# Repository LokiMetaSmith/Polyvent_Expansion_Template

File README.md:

# Polyvent_Expansion_Template
This project is a bare template board for generating new Polyvent Expansion Cards

<a href="Schematic.gif">Schematic screen shot     
</a>  

<a href="Schematic.gif">PCB screen shot   
</a>

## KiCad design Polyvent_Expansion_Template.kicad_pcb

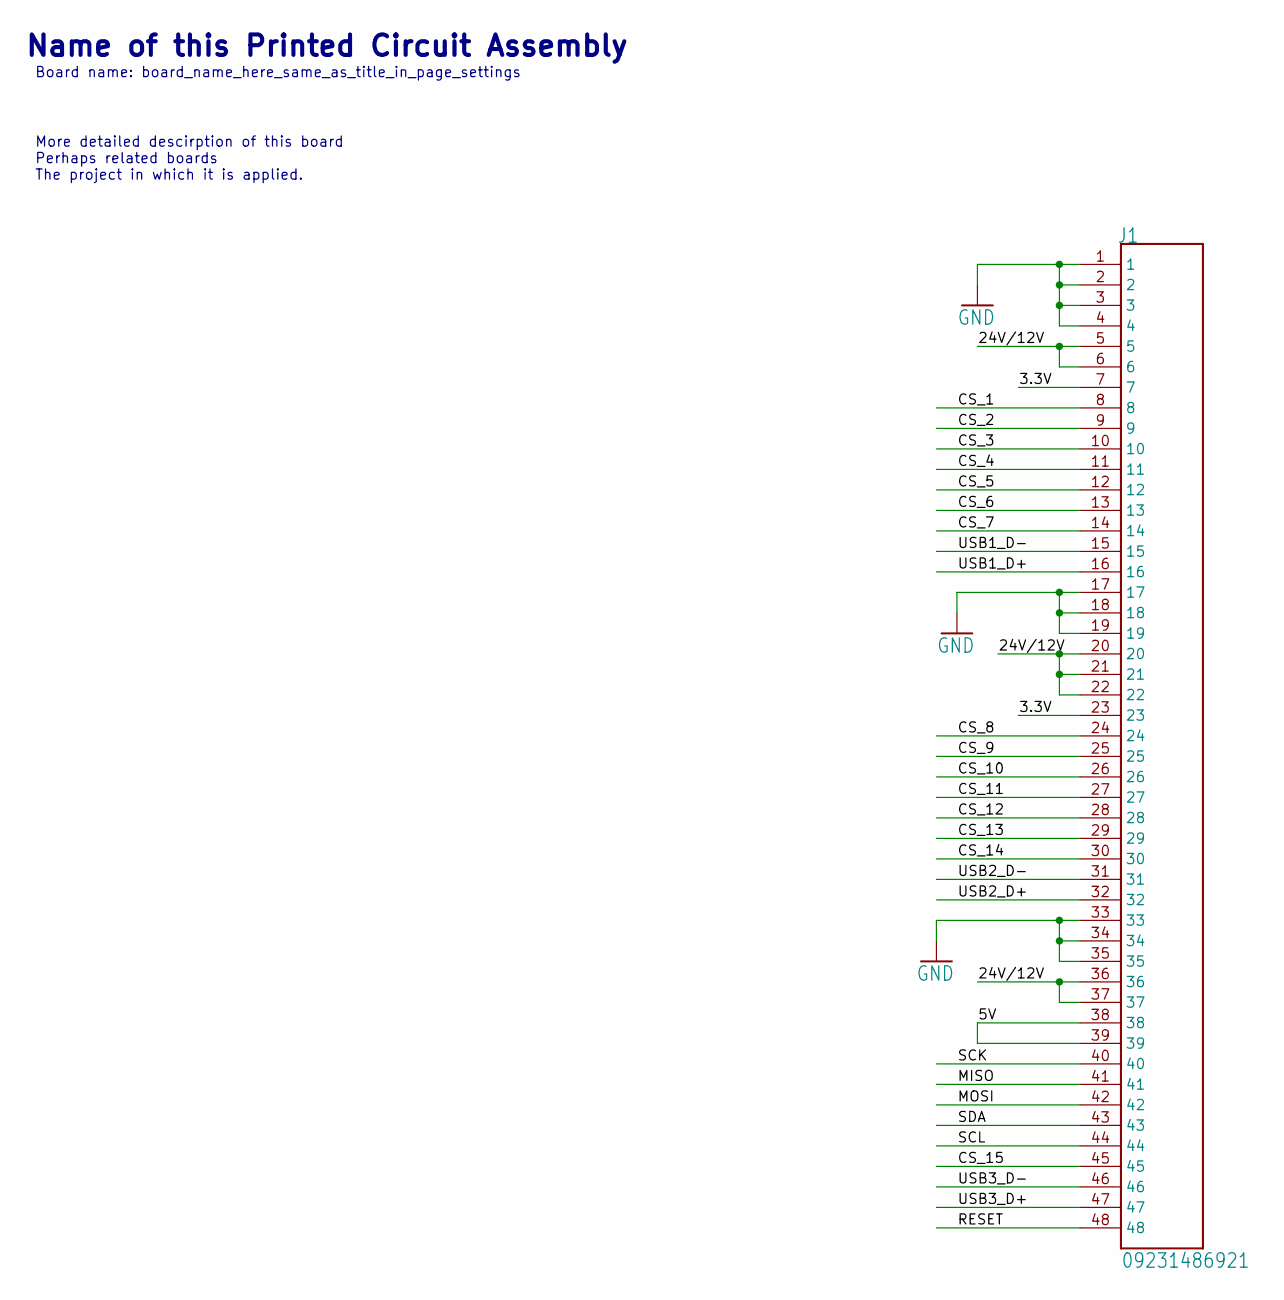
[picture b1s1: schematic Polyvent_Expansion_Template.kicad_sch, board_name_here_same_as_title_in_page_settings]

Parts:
J1: 09231486921; HARTING_09231486921

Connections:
3.3V: J1.7, J1.23
5V: J1.38, J1.39
24V/12V: J1.5, J1.6, J1.20, J1.21, J1.22, J1.36, J1.37
CS_1: J1.8
CS_2: J1.9
CS_3: J1.10
CS_4: J1.11
CS_5: J1.12
CS_6: J1.13
CS_7: J1.14
CS_8: J1.24
CS_9: J1.25
CS_10: J1.26
CS_11: J1.27
CS_12: J1.28
CS_13: J1.29
CS_14: J1.30
CS_15: J1.45
GND: J1.1, J1.2, J1.3, J1.4, J1.17, J1.18, J1.19, J1.33, J1.34, J1.35
MISO: J1.41
MOSI: J1.42
RESET: J1.48
SCK: J1.40
SCL: J1.44
SDA: J1.43
USB1_D+: J1.16
USB1_D-: J1.15
USB2_D+: J1.32
USB2_D-: J1.31
USB3_D+: J1.47
USB3_D-: J1.46

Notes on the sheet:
Board name: board_name_here_same_as_title_in_page_settings
More detailed descirption of this board Perhaps related boards The project in which it is applied.
Name of this Printed Circuit Assembly

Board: 2 copper layers, 6 parts (0 on the bottom side), 4 nets, no tracks yet.

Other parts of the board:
@HOLE0, @HOLE1, @HOLE2, @HOLE3: (no value)
Graphic1: OSHW-Logo2_7.3x6mm_SilkScreen

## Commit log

2022-10-07 Add files via upload
    Initial commmit
2022-10-27 Add defaults to schematic and PCB including license and Public Invetion Name. Lock the connector on PCB.
2022-10-27 Update README.md with screen shots of schematic and PCB.
2022-10-27 Update README.md
    Change HTML to display thumbnail of Schematic and PCB.

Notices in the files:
Polyvent_Expansion_Template.kicad_pcb:
GNU Affero General Public License v3.0
CERN Open Hardware License Version 2 - Strongly Reciprocal
